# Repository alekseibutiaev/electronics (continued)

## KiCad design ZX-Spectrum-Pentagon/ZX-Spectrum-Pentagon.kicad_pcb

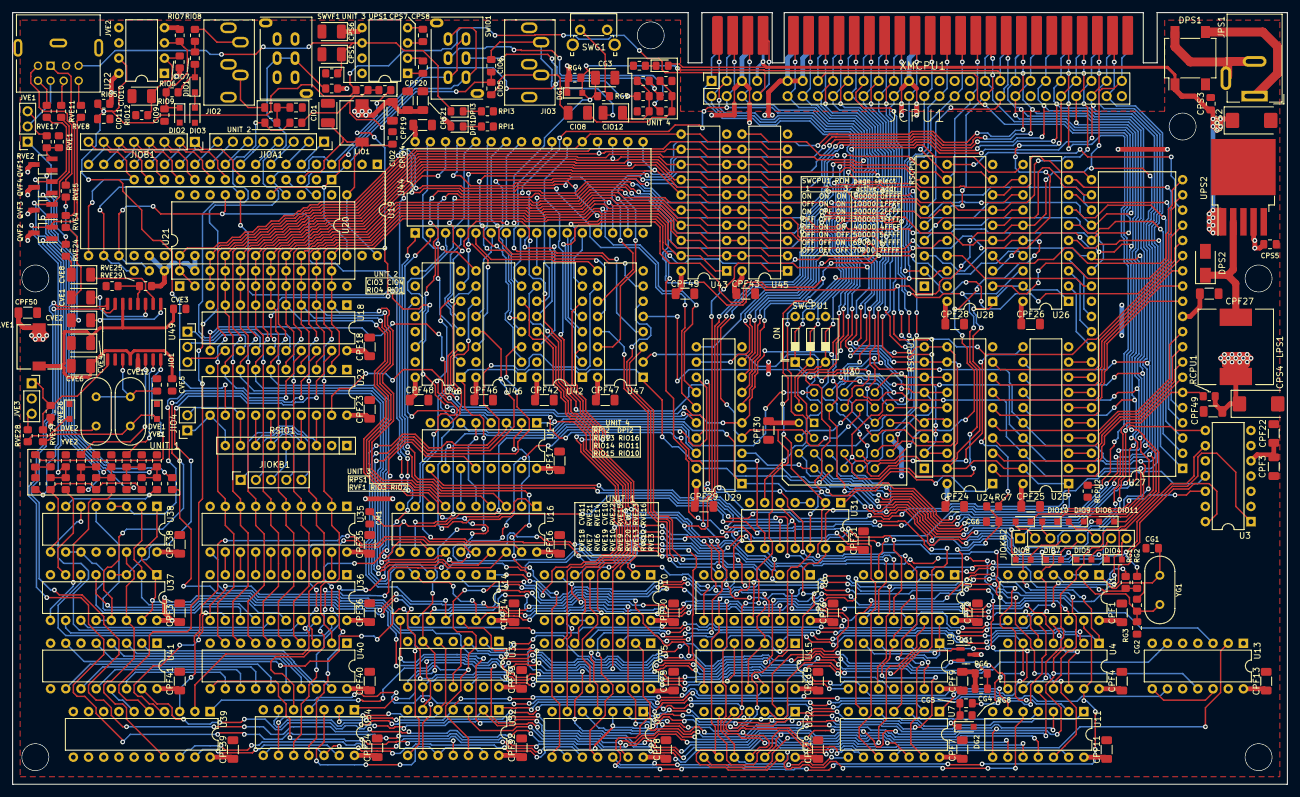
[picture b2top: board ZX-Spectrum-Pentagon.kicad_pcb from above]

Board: 2 copper layers, 213.1 x 129.0 mm, 251 parts (0 on the bottom side), 347 nets.

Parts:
CG1, CG2: 20pF; C_0805_2012Metric_Pad1.18x1.45mm_HandSolder
CG3: 47uF/16V; CP_EIA-3528-21_Kemet-B_Pad1.50x2.35mm_HandSolder
CG4: 1nF; C_0805_2012Metric_Pad1.18x1.45mm_HandSolder
CG5: 22nF; C_0805_2012Metric_Pad1.18x1.45mm_HandSolder
CG6: 510pF; C_0805_2012Metric_Pad1.18x1.45mm_HandSolder
CIO1: 47uF/16V; CP_EIA-3528-21_Kemet-B_Pad1.50x2.35mm_HandSolder
CIO2, CIO11: 100nF; C_0805_2012Metric_Pad1.18x1.45mm_HandSolder
CIO3, CIO5, CIO6, CIO7: 150nF; C_0805_2012Metric_Pad1.18x1.45mm_HandSolder
CIO4: 3.3nF; C_0805_2012Metric_Pad1.18x1.45mm_HandSolder
CIO8, CIO10, CIO12: 10uF/16V; CP_EIA-3528-21_Kemet-B_Pad1.50x2.35mm_HandSolder
CIO9: 1nF; C_0805_2012Metric_Pad1.18x1.45mm_HandSolder
CM1: 1nF; C_0805_2012Metric_Pad1.18x1.45mm_HandSolder
CPF1, CPF2, CPF3, CPF4, CPF5, CPF6, CPF7, CPF8, CPF9, CPF10, CPF11, CPF12, CPF13, CPF14, CPF15, CPF16, CPF17, CPF18, CPF19, CPF20, CPF21, CPF22, CPF23, CPF24, CPF25, CPF26, CPF27, CPF28, CPF29, CPF30, CPF31, CPF32, CPF33, CPF34, CPF35, CPF36, CPF37, CPF38, CPF39, CPF40, CPF41, CPF42, CPF43, CPF44, CPF45, CPF46, CPF47, CPF48, CPF49, CPF50: 100nF; C_1206_3216Metric_Pad1.33x1.80mm_HandSolder
CPS1, CPS6: 4.7uF/16V; CP_EIA-3528-21_Kemet-B_Pad1.50x2.35mm_HandSolder
CPS2, CPS4: 330uF/16V; CP_EIA-7343-31_Kemet-D_Pad2.25x2.55mm_HandSolder
CPS3, CPS5: 100nF; C_0805_2012Metric_Pad1.18x1.45mm_HandSolder
CPS7, CPS8: 1uF; C_0805_2012Metric_Pad1.18x1.45mm_HandSolder
CVE1, CVE2, CVE8: 220uF/6V; CP_EIA-3528-21_Kemet-B_Pad1.50x2.35mm_HandSolder
CVE3, CVE5, CVE7, CVE10, CVE11: 100nF; C_0805_2012Metric_Pad1.18x1.45mm_HandSolder
CVE4, CVE6: 47uF/16V; CP_EIA-3528-21_Kemet-B_Pad1.50x2.35mm_HandSolder
CVE12: 5pF; C_0805_2012Metric_Pad1.18x1.45mm_HandSolder
DG1, DG2: 1N4148; D_SOD-323_HandSoldering
DIO1, DIO3: BZX35450-C3V0X; D_SOD-323_HandSoldering
DIO2, DIO4, DIO5, DIO6, DIO7, DIO8, DIO9, DIO10, DIO11: 1N4148; D_SOD-323_HandSoldering
DPI1: RED; LED_0805_2012Metric_Pad1.15x1.40mm_HandSolder
DPI2: YELLO; LED_0805_2012Metric_Pad1.15x1.40mm_HandSolder
DPI3: GREEN; LED_0805_2012Metric_Pad1.15x1.40mm_HandSolder
DPS1: DF005S; Diode_Bridge_Vishay_DFS
DPS2: SK810; D_SMA
DVE1, DVE2: 1N4148; D_SOD-323_HandSoldering
JCPU1: Conn_02x28; PinSocket_2x28_P2.54mm_Vertical
JIO1: Conn_01x03_Female; PinSocket_1x03_P2.54mm_Vertical
JIO2, JIO3: AudioJack; Jack_3.5mm_CUI_SJ1-3535NG_Vertical
JIO4: Conn_01x02_Female; PinSocket_1x02_P2.54mm_Vertical
JIOA1: Conn_01x08_Female; PinSocket_1x08_P2.54mm_Vertical
JIOB1: Conn_01x08_Female; PinSocket_1x08_P2.54mm_Vertical
JIOKB1: Conn_01x05_Female; PinSocket_1x05_P2.54mm_Vertical
JIOKB2: Conn_01x08_Female; PinSocket_1x08_P2.54mm_Vertical
JPS1: Power_Jack; BarrelJack_Wuerth_6941xx301002
JVE1: SYNC/CVIDEO; PinSocket_1x03_P2.54mm_Vertical
JVE2: SVIDEO; CUI_MD-80SMK
JVE3: PAL/NTSC; PinSocket_1x03_P2.54mm_Vertical
LIO1: 100uH; L_7.3x7.3_H4.5
LPS1: 33uH; L_12x12mm_H6mm
LVE1: 100uH; L_7.3x7.3_H4.5
QG1: BC848; SOT-23
QVF1, QVF2, QVF3, QVF4: BC848; SOT-23_Handsoldering
RCPU1: 330; R_0805_2012Metric_Pad1.20x1.40mm_HandSolder
RCPU2: 10kOm; R_0805_2012Metric_Pad1.20x1.40mm_HandSolder
RG1, RG8: 1kOm; R_0805_2012Metric_Pad1.20x1.40mm_HandSolder
RG2, RG4: 10kOm; R_0805_2012Metric_Pad1.20x1.40mm_HandSolder
RG3: 2MOm; R_0805_2012Metric_Pad1.20x1.40mm_HandSolder
RG5: 330; R_0805_2012Metric_Pad1.20x1.40mm_HandSolder
RG6: 160; R_0805_2012Metric_Pad1.20x1.40mm_HandSolder
RG7: 680; R_0805_2012Metric_Pad1.20x1.40mm_HandSolder
RIO1, RIO3, RIO4: 47kOm; R_0805_2012Metric_Pad1.20x1.40mm_HandSolder
RIO2: 10kOm; R_0805_2012Metric_Pad1.20x1.40mm_HandSolder
RIO5: 2.2kOm; R_0805_2012Metric_Pad1.20x1.40mm_HandSolder
RIO6, RIO11, RIO13: 4.7kOm; R_0805_2012Metric_Pad1.20x1.40mm_HandSolder
RIO7: 100kOm; R_0805_2012Metric_Pad1.20x1.40mm_HandSolder
RIO8: 1kOm; R_0805_2012Metric_Pad1.20x1.40mm_HandSolder
RIO9, RIO15, RIO16: 330; R_0805_2012Metric_Pad1.20x1.40mm_HandSolder
RIO10, RIO14: 3.0kOm; R_0805_2012Metric_Pad1.20x1.40mm_HandSolder
RIO12: 160; R_0805_2012Metric_Pad1.20x1.40mm_HandSolder
RPI1, RPI2, RPI3: 330; R_0805_2012Metric_Pad1.20x1.40mm_HandSolder
RPS1: 4.7kOm; R_0805_2012Metric_Pad1.20x1.40mm_HandSolder
RSCPU1, RSCPU2: 8x10kOm; R_Array_SIP9
RSIO1: 8x10kOm; R_Array_SIP9
RVE1, RVE2: 270; R_0805_2012Metric_Pad1.20x1.40mm_HandSolder
RVE3: 680; R_0805_2012Metric_Pad1.20x1.40mm_HandSolder
RVE4, RVE5, RVE21, RVE22, RVE23, RVE24: 75; R_0805_2012Metric_Pad1.20x1.40mm_HandSolder
RVE6, RVE9, RVE12: 3.9kOm; R_0805_2012Metric_Pad1.20x1.40mm_HandSolder
RVE7, RVE10, RVE13: 18kOm; R_0805_2012Metric_Pad1.20x1.40mm_HandSolder
RVE8, RVE11, RVE17, RVE18, RVE19, RVE20: 68; R_0805_2012Metric_Pad1.20x1.40mm_HandSolder
RVE14, RVE15, RVE16: 2.2kOm; R_0805_2012Metric_Pad1.20x1.40mm_HandSolder
RVE25: 0Om; R_0805_2012Metric_Pad1.20x1.40mm_HandSolder
RVE26, RVE27, RVE28, RVE29: 10kOm; R_0805_2012Metric_Pad1.20x1.40mm_HandSolder
RVF1: 4.7kOm; R_0805_2012Metric_Pad1.20x1.40mm_HandSolder
SWCPU1: ROMSELECT; SW_DIP_SPSTx03_Slide_6.7x9.18mm_W7.62mm_P2.54mm_LowProfile
SWG1: RESET; SW_Tactile_SPST_Angled_PTS645Vx39-2LFS
SWIO1: ABC/ACB; PS-22F03
SWVF1: 128K/512K; PS-22F03
U1, U7: 74HC04; DIP-14_W7.62mm
U2: 74HC14; DIP-14_W7.62mm
U3: 74HC93; DIP-14_W7.62mm
U4: 74HC11; DIP-14_W7.62mm
U5, U10: 74HC193; DIP-16_W7.62mm
U6, U17, U42, U46, U47, U48: 74HC257; DIP-16_W7.62mm
U8, U32: 74HC00; DIP-14_W7.62mm
U9: 74HC86; DIP-14_W7.62mm
U11: 74HC02; DIP-14_W7.62mm
U12, U34: 74HC08; DIP-14_W7.62mm
U13, U15, U33: 74HC74; DIP-14_W7.62mm
U14: 74HC393; DIP-14_W7.62mm
U16: 74HC273; DIP-20_W7.62mm
U18, U35, U36, U40, U45: 74HC574; DIP-20_W7.62mm
U19: AY-3-8910; DIP-40_W15.24mm
U20: AY-3-8912_DUMMY; DIP-28_W15.24mm
U21: AY-3-8913_DUMMY; DIP-24_W15.24mm
U22: LM311; DIP-8_W7.62mm
U23, U24: 74HC245; DIP-20_W7.62mm
U25, U26, U43: 74HC541; DIP-20_W7.62mm
U27: Z80CPU; DIP-40_W15.24mm
U28: 74HC244; DIP-20_W7.62mm
U29, U39: GAL16V8; DIP-20_W7.62mm
U30: 29F040; PLCC-32_THT-Socket
U31: 74HC32; DIP-14_W7.62mm
U37, U38: 74HC153; DIP-16_W7.62mm
U41: 74HC166; DIP-16_W7.62mm
U44: HM628512; DIP-32_W15.24mm
U49: AD724; SOIC-16W_7.5x10.3mm_P1.27mm
UPS1: ST662; DIP-8_W7.62mm
UPS2: LM2596S-5.0V; TO-263-5_TabPin3
XMCPU1: EDGE-28M5; EDGE_28M5-2.54
YG1: 14MHZ; Crystal_HC49-U_Vertical
YVE1: 3.579545MHz OR 14.318180MHz; Crystal_HC49-U_Vertical
YVE2: 4.433619MHz OR 17.734480MHz; Crystal_HC49-U_Vertical

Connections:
+9V: CPS2.1, CPS3.1, DPI2.2 (A), DPS1.1 (+), JCPU1.7, UPS2.1 (VIN), XMCPU1.A4
/+12V: CPS1.1, DPI3.2 (A), JVE2.5, RPS1.1, UPS1.6 (VOut)
/A0: JCPU1.17, U26.16 (B2), U29.8 (I6), U30.12 (A0), U42.5 (A1), XMCPU1.A9
/A1: JCPU1.19, U26.17 (B1), U29.6 (I4), U30.11 (A1), U42.2 (A0), XMCPU1.A10
/A2: JCPU1.21, U26.18 (B0), U30.10 (A2), U42.14 (A3), XMCPU1.A11
/A3: JCPU1.23, U25.11 (B7), U30.9 (A3), U42.11 (A2), XMCPU1.A12
/A4: JCPU1.47, U25.12 (B6), U30.8 (A4), U46.5 (A1), XMCPU1.A24
/A5: JCPU1.45, U25.13 (B5), U29.2 (I0), U30.7 (A5), U46.2 (A0), XMCPU1.A23
/A6: JCPU1.43, U25.14 (B4), U30.6 (A6), U46.14 (A3), XMCPU1.A22
/A7: JCPU1.41, U25.15 (B3), U29.3 (I1), U30.5 (A7), U47.11 (A2), XMCPU1.A21
/A8: DIO6.1 (K), JCPU1.52, U25.16 (B2), U30.27 (A8), U47.14 (A3), XMCPU1.B26
/A9: DIO9.1 (K), JCPU1.53, U25.17 (B1), U30.26 (A9), U47.5 (A1), XMCPU1.A27
/A10: DIO10.1 (K), JCPU1.54, U25.18 (B0), U30.23 (A10), U47.2 (A0), XMCPU1.B27
/A11: DIO11.1 (K), JCPU1.55, U26.15 (B3), U30.25 (A11), U48.5 (A1), XMCPU1.A28
/A12: DIO8.1 (K), JCPU1.3, U26.14 (B4), U30.4 (A12), U48.2 (A0), XMCPU1.A2
/A13: DIO7.1 (K), JCPU1.4, U26.13 (B5), U30.28 (A13), U48.14 (A3), XMCPU1.B2
/A14: DIO5.1 (K), JCPU1.1, U8.5 (B), U17.3 (B0), U17.10 (B2), U26.12 (B6), U29.5 (I3), U31.13 (B), XMCPU1.A1
/A14-ROM: U16.12 (Q4), U30.29 (A14)
/A15: DIO4.1 (K), JCPU1.2, U8.4 (A), U17.6 (B1), U26.11 (B7), U29.1 (CLK), U31.12 (A), XMCPU1.B1
/AYCLK: U3.11 (QB2), U19.22 (CLK), U20.15 (CLK), U21.20 (CLK)
/BC1: U19.29 (BC1), U20.20 (BC1), U21.3 (BC1), U29.15 (IO5)
/BDIR: U19.27 (BDIR), U20.18 (BDIR), U21.2 (BDIR), U29.14 (IO6)
/BL: CG4.1, QG1.2 (E), RG6.2, U37.1 (~G0), U37.15 (~G1), U38.1 (~G0), U38.15 (~G1)
/C3: U1.12 (~Y), U36.11 (C)
/C5: U13.6 (~Q), U37.2 (SE1), U38.2 (SE1)
/C16: U7.10 (~Y), U43.1 (~OE0), U43.19 (~OE1), U44.29 (~WE)
/C17: U32.8 (~Y), U35.11 (C)
/C18: U32.11 (~Y), U40.11 (C)
/C19: U8.11 (~Y), U45.1 (~OE)
/C20: U11.12 (B), U32.6 (~Y), U45.11 (C)
/C25: RCPU1.1, U1.6 (~Y), U4.1 (A), U15.2 (D), U27.6 (~CLK)
/C29: U9.9 (A), U11.6 (B), U32.9 (A), U33.9 (Q)
/C30: U6.1 (~A/B), U32.12 (A), U33.8 (~Q)
/C31: U2.2 (~Y), U2.3 (A), U15.3 (C), U15.11 (C)
/CBRDB: U18.19 (Q0), U37.3 (D03), U37.4 (D02)
/CBRDG: U18.17 (Q2), U38.3 (D03), U38.4 (D02)
/CBRDR: U18.18 (Q1), U37.12 (D12), U37.13 (D13)
/CPU: U32.5 (B), U33.5 (Q), U34.9 (A)
/CPU/BUSACK: U2.6 (~Y), U24.19 (~OE), U25.1 (~OE0), U25.19 (~OE1), U26.1 (~OE0), U26.19 (~OE1), U28.1 (~OE)
/CPU/DIR: U24.1 (A/~B), U29.19 (IO1)
/CPU/RA15: JCPU1.40, RSCPU2.6 (R5), U30.3 (A15), XMCPU1.B20
/CPU/RA16: RSCPU2.7 (R6), SWCPU1.1, U30.2 (A16)
/CPU/RA17: RSCPU2.8 (R7), SWCPU1.2, U30.30 (A17)
/CPU/RA18: RSCPU2.9 (R8), SWCPU1.3, U30.1 (A18)
/CPU/xA0: U26.4 (A2), U27.30 (A0)
/CPU/xA1: U26.3 (A1), U27.31 (A1)
/CPU/xA2: U26.2 (A0), U27.32 (A2)
/CPU/xA3: U25.9 (A7), U27.33 (A3)
/CPU/xA4: U25.8 (A6), U27.34 (A4)
/CPU/xA5: U25.7 (A5), U27.35 (A5)
/CPU/xA6: U25.6 (A4), U27.36 (A6)
/CPU/xA7: U25.5 (A3), U27.37 (A7)
/CPU/xA8: U25.4 (A2), U27.38 (A8)
/CPU/xA9: U25.3 (A1), U27.39 (A9)
/CPU/xA10: U25.2 (A0), U27.40 (A10)
/CPU/xA11: U26.5 (A3), U27.1 (A11)
/CPU/xA12: U26.6 (A4), U27.2 (A12)
/CPU/xA13: U26.7 (A5), U27.3 (A13)
/CPU/xA14: U26.8 (A6), U27.4 (A14)
/CPU/xA15: U26.9 (A7), U27.5 (A15)
/CPU/xD0: U24.8 (A6), U27.14 (D0)
/CPU/xD1: U24.9 (A7), U27.15 (D1)
/CPU/xD2: U24.6 (A4), U27.12 (D2)
/CPU/xD3: U24.3 (A1), U27.8 (D3)
/CPU/xD4: U24.2 (A0), U27.7 (D4)
/CPU/xD5: U24.4 (A2), U27.9 (D5)
/CPU/xD6: U24.5 (A3), U27.10 (D6)
/CPU/xD7: U24.7 (A5), U27.13 (D7)
/CPU/~BUSACK: JCPU1.51, U2.5 (A), U28.7 (B1), XMCPU1.A26
/CPU/~BUSRQ: JCPU1.37, RSCPU2.4 (R3), U27.25 (~BUSRQ), XMCPU1.A19
/CPU/~DI_ULA: JCPU1.25, U29.12 (IO8), XMCPU1.A13
/CPU/~HALT: JCPU1.30, U28.9 (B0), XMCPU1.B15
/CPU/~IORQ: JCPU1.34, U28.16 (B1), U29.7 (I5), XMCPU1.B17
/CPU/~M1: JCPU1.48, U28.5 (B2), U29.9 (I7), XMCPU1.B24
/CPU/~NMI: JCPU1.28, RSCPU2.2 (R1), U27.17 (~NMI), XMCPU1.B14
/CPU/~ROMCE: U30.22 (~CE), U31.6 (Y)
/CPU/~ROMCS: JCPU1.49, RCPU2.1, U31.1 (A), XMCPU1.A25
/CPU/~WAIT: JCPU1.42, RSCPU2.5 (R4), U27.24 (~WAIT), XMCPU1.B21
/CPU/~WR: JCPU1.38, U28.14 (B2), U29.11 (~OE/I8), XMCPU1.B19
/CPU/~xBUSACK: U27.23 (~BUSACK), U28.13 (A1)
/CPU/~xHALT: U27.18 (~HALT), U28.11 (A0)
/CPU/~xIORQ: U27.20 (~IORQ), U28.4 (A1)
/CPU/~xM1: U27.27 (~M1), U28.15 (A2)
/CPU/~xMREQ: U27.19 (~MREQ), U28.2 (A0)
/CPU/~xRD: U27.21 (~RD), U28.8 (A3)
/CPU/~xRFSH: U27.28 (~RFSH), U28.17 (A3)
/CPU/~xWR: U27.22 (~WR), U28.6 (A2)
/CS_32765: CM1.1, U16.11 (WR), U29.18 (IO2)
/D0: JCPU1.12, RSCPU1.8 (R7), U16.3 (D0), U18.2 (D0), U19.37 (D0), U20.28 (D0), U21.11 (D0), U23.2 (A0), U24.12 (B6), U30.13 (D0), U43.2 (A0), U45.19 (Q0), XMCPU1.B6
/D1: JCPU1.14, RSCPU1.9 (R8), U16.4 (D1), U18.3 (D1), U19.36 (D1), U20.27 (D1), U21.10 (D1), U23.3 (A1), U24.11 (B7), U30.14 (D1), U43.3 (A1), U45.18 (Q1), XMCPU1.B7
/D2: JCPU1.16, RSCPU1.6 (R5), U16.7 (D2), U18.4 (D2), U19.35 (D2), U20.26 (D2), U21.9 (D2), U23.4 (A2), U24.14 (B4), U30.15 (D2), U43.4 (A2), U45.17 (Q2), XMCPU1.B8
/D3: JCPU1.22, RSCPU1.3 (R2), U16.8 (D3), U18.5 (D3), U19.34 (D3), U20.25 (D3), U21.8 (D3), U23.5 (A3), U24.17 (B1), U30.17 (D3), U43.5 (A3), U45.16 (Q3), XMCPU1.B11
/D4: JCPU1.24, RSCPU1.2 (R1), U16.13 (D4), U18.6 (D4), U19.33 (D4), U20.24 (D4), U21.7 (D4), U23.6 (A4), U24.18 (B0), U30.18 (D4), U43.6 (A4), U45.15 (Q4), XMCPU1.B12
/D5: JCPU1.20, RSCPU1.4 (R3), U16.14 (D5), U18.7 (D5), U19.32 (D5), U20.23 (D5), U21.6 (D5), U23.7 (A5), U24.16 (B2), U30.19 (D5), U43.7 (A5), U45.14 (Q5), XMCPU1.B10
/D6: JCPU1.18, RSCPU1.5 (R4), U16.17 (D6), U18.8 (D6), U19.31 (D6), U20.22 (D6), U21.5 (D6), U23.8 (A6), U24.15 (B3), U30.20 (D6), U43.8 (A6), U45.13 (Q6), XMCPU1.B9
/D7: JCPU1.6, RSCPU1.7 (R6), U16.18 (D7), U18.9 (D7), U19.30 (D7), U20.21 (D7), U21.4 (D7), U23.9 (A7), U24.13 (B5), U30.21 (D7), U43.9 (A7), U45.12 (Q7), XMCPU1.B3
/DISPLAY: U4.11 (C), U9.10 (B), U31.9 (A), U33.6 (~Q), U34.1 (A), U42.1 (~A/B), U46.1 (~A/B), U47.1 (~A/B), U48.1 (~A/B)
/DI_32765: U16.15 (Q5), U29.13 (IO7)
/F25Hz: U13.9 (Q), U39.1 (CLK)
/FSYNC: U9.6 (Y), U9.13 (B)
/GPA6: U34.13 (B), U39.19 (IO1)
/GPA7: U8.10 (B), U39.18 (IO2)
/Generator/B6: U3.12 (QA0), U6.6 (B1), U14.1 (C)
/Generator/B7: U6.13 (B3), U14.3 (Q0)
/Generator/B8: U6.3 (B0), U14.4 (Q1)
/Generator/B12: U6.5 (A1), U6.10 (B2), U12.9 (A), U12.13 (B), U14.10 (Q1)
/Generator/B13: U6.14 (A3), U11.5 (A), U12.10 (B), U14.9 (Q2)
/Generator/B50: U10.7 (Q3), U11.3 (B), U12.4 (A)
/Generator/B51: U11.9 (B), U12.12 (A), U14.8 (Q3)
/Generator/C6: U11.10 (~Y), U12.5 (B)
/HSYNC: U3.14 (CA), U8.3 (~Y), U9.4 (A), U49.16 (HSYNC)
/InputOutput/CHA: RIO14.1, U19.4 (ACHA), U20.5 (ACHA), U21.17 (ACHA)
/InputOutput/CHB: SWIO1.1 (A), SWIO1.6 (C), U19.3 (ACHB), U20.4 (ACHB), U21.15 (ACHB)
/InputOutput/CHC: SWIO1.3 (C), SWIO1.4 (A), U19.38 (ACHC), U20.1 (ACHC), U21.18 (ACHC)
/InputOutput/IND5: JIO4.2, RSIO1.8 (R7), U23.13 (B5)
/InputOutput/IND7: JIO4.1, RSIO1.9 (R8), U23.11 (B7)
/InputOutput/IOA0: JIOB1.8, U19.21 (IOA0), U20.14 (IOA0)
/InputOutput/IOA1: JIOB1.7, U19.20 (IOA1), U20.13 (IOA1)
/InputOutput/IOA2: JIOB1.6, U19.19 (IOA2), U20.12 (IOA2)
/InputOutput/IOA3: JIOB1.5, U19.18 (IOA3), U20.11 (IOA3)
/InputOutput/IOA4: JIOB1.4, U19.17 (IOA4), U20.10 (IOA4)
/InputOutput/IOA5: JIOB1.3, U19.16 (IOA5), U20.9 (IOA5)
/InputOutput/IOA6: JIOB1.2, U19.15 (IOA6), U20.8 (IOA6)
/InputOutput/IOA7: JIOB1.1, U19.14 (IOA7), U20.7 (IOA7)
/InputOutput/IOB0: JIOA1.8, U19.13 (IOB0)
/InputOutput/IOB1: JIOA1.7, U19.12 (IOB1)
/InputOutput/IOB2: JIOA1.6, U19.11 (IOB2)
/InputOutput/IOB3: JIOA1.5, U19.10 (IOB3)
/InputOutput/IOB4: JIOA1.4, U19.9 (IOB4)
/InputOutput/IOB5: JIOA1.3, U19.8 (IOB5)
/InputOutput/IOB6: JIOA1.2, U19.7 (IOB6)
/InputOutput/IOB7: JIOA1.1, U19.6 (IOB7)
/InputOutput/KBA8: DIO6.2 (A), JIOKB2.6
/InputOutput/KBA9: DIO9.2 (A), JIOKB2.3
/InputOutput/KBA10: DIO10.2 (A), JIOKB2.2
/InputOutput/KBA11: DIO11.2 (A), JIOKB2.1
/InputOutput/KBA12: DIO8.2 (A), JIOKB2.4
/InputOutput/KBA13: DIO7.2 (A), JIOKB2.5
/InputOutput/KBA14: DIO5.2 (A), JIOKB2.7
/InputOutput/KBA15: DIO4.2 (A), JIOKB2.8
/InputOutput/KBD0: JIOKB1.1, RSIO1.3 (R2), U23.18 (B0)
/InputOutput/KBD1: JIOKB1.2, RSIO1.4 (R3), U23.17 (B1)
/InputOutput/KBD2: JIOKB1.3, RSIO1.5 (R4), U23.16 (B2)
/InputOutput/KBD3: JIOKB1.4, RSIO1.6 (R5), U23.15 (B3)
/InputOutput/KBD4: JIOKB1.5, RSIO1.7 (R6), U23.14 (B4)
/InputOutput/OURD5: JIO1.1, U18.14 (Q5)
/InputOutput/OURD6: JIO1.2, U18.13 (Q6)
/InputOutput/OURD7: JIO1.3, U18.12 (Q7)
/InputOutput/TYPEOUTTTL: RIO1.1, RIO4.1, U18.16 (Q3)
/InputOutput/TapeIn: JIO2.T, RIO8.1
/InputOutput/TapeOut: CIO3.2, JIO2.R
/MD0: U35.2 (D0), U40.2 (D0), U43.18 (B0), U44.13 (D0), U45.2 (D0)
/MD1: U35.3 (D1), U40.3 (D1), U43.17 (B1), U44.14 (D1), U45.3 (D1)
/MD2: U35.4 (D2), U40.4 (D2), U43.16 (B2), U44.15 (D2), U45.4 (D2)
/MD3: U35.5 (D3), U40.5 (D3), U43.15 (B3), U44.17 (D3), U45.5 (D3)
/MD4: U35.6 (D4), U40.6 (D4), U43.14 (B4), U44.18 (D4), U45.6 (D4)
/MD5: U35.7 (D5), U40.7 (D5), U43.13 (B5), U44.19 (D5), U45.7 (D5)
/MD6: U35.8 (D6), U40.8 (D6), U43.12 (B6), U44.20 (D6), U45.8 (D6)
/MD7: U35.9 (D7), U40.9 (D7), U43.11 (B7), U44.21 (D7), U45.9 (D7)
/MX0: U17.4 (Y0), U48.11 (A2)
/MX1: U17.7 (Y1), U46.11 (A2)
/MX2: U17.9 (Y2), U31.10 (B)
/MX3: U17.12 (Y3), U34.10 (B)
/Memory/MA0: U42.7 (Y1), U44.12 (A0)
/Memory/MA1: U42.4 (Y0), U44.11 (A1)
/Memory/MA2: U42.12 (Y3), U44.10 (A2)
/Memory/MA3: U42.9 (Y2), U44.9 (A3)
/Memory/MA4: U44.8 (A4), U46.7 (Y1)
/Memory/MA5: U44.7 (A5), U46.4 (Y0)
/Memory/MA6: U44.6 (A6), U46.12 (Y3)
/Memory/MA7: U44.5 (A7), U47.9 (Y2)
/Memory/MA8: U44.27 (A8), U47.12 (Y3)
/Memory/MA9: U44.26 (A9), U47.7 (Y1)
/Memory/MA10: U44.23 (A10), U47.4 (Y0)
/Memory/MA11: U44.25 (A11), U48.7 (Y1)
/Memory/MA12: U44.4 (A12), U48.4 (Y0)
/Memory/MA13: U44.28 (A13), U48.12 (Y3)
/Memory/MA14: U44.3 (A14), U48.9 (Y2)
/Memory/MA15: U44.31 (A15), U46.9 (Y2)
/Memory/MA16: U31.8 (Y), U44.2 (A16)
/Memory/MA17: U34.11 (~Y), U44.30 (A17)
/Memory/MA18: U8.8 (~Y), U44.1 (A18)
/PA6: U16.16 (Q6), U39.2 (I0)
/PA7: U16.19 (Q7), U39.3 (I1)
/PowerSources/PowA: DPS1.3, JPS1.1
/PowerSources/PowB: DPS1.4, JPS1.2, JPS1.3
/RAS: U15.5 (Q), U15.12 (D), U32.4 (A), U34.2 (B)
/SA0: U5.6 (Q2), U13.3 (C), U42.6 (B1)
/SA1: U5.7 (Q3), U42.3 (B0)
/SA2: U7.1 (A), U10.3 (Q0), U42.13 (B3)
/SA3: U10.2 (Q1), U11.2 (A), U42.10 (B2)
/SA4: U10.6 (Q2), U12.2 (B), U46.6 (B1)
/SA5: U14.5 (Q2), U46.3 (B0)
/SA6: U4.4 (B), U14.6 (Q3), U14.13 (C), U46.13 (B3)
/SA7: U4.5 (C), U14.11 (Q0), U47.10 (B2)
/SA8: U6.7 (Y1), U47.13 (B3)
/SA9: U6.12 (Y3), U47.6 (B1)
/SA10: U6.4 (Y0), U47.3 (B0)
/SA11: U6.9 (Y2), U48.6 (B1)
/SA12: U7.4 (~Y), U48.3 (B0)
/SCRSEL: U16.9 (Q3), U46.10 (B2)
/TAPEINTTL: CIO11.2, JCPU1.8, RIO3.2, RIO5.1, U22.7, U23.12 (B6), XMCPU1.B4
/TTLB: RVE6.2, U37.7 (Y0)
/TTLG: RVE12.2, U38.7 (Y0)
/TTLR: RVE9.2, U37.9 (Y1)
/TTLSYNC: RVE3.2, U9.11 (Y)
/TTLY: RVE7.2, RVE10.2, RVE13.2, U38.9 (Y1)
/VSYNC: U2.12 (~Y), U49.15 (VSYNC)
/VideoEncoder/BLUE: JVE2.8, RVE8.2
/VideoEncoder/CRMA: JVE2.3, RVE5.1
/VideoEncoder/CVIDEO: JVE1.1, RVE24.1
/VideoEncoder/GREEN: JVE2.6, RVE17.2
/VideoEncoder/LUMA: JVE2.1, RVE4.1
/VideoEncoder/RED: JVE2.7, RVE11.2
/VideoEncoder/SYNC: JVE1.3, RVE2.1
/VideoEncoder/VIDEO: JVE1.2, JVE2.4
/VideoFormating/512KMOD: RVF1.2, SWVF1.2 (B), SWVF1.5 (B), U39.5 (I3)
/VideoFormating/BLUE_B: U36.16 (Q3), U37.5 (D01)
/VideoFormating/BLUE_F: U36.19 (Q0), U37.6 (D00)
/VideoFormating/BRIGHT: U36.13 (Q6), U38.10 (D10), U38.11 (D11)
/VideoFormating/FLASL_BIT: U36.12 (Q7), U39.4 (I2)
/VideoFormating/GREEN_B: U36.14 (Q5), U38.5 (D01)
/VideoFormating/GREEN_F: U36.17 (Q2), U38.6 (D00)
/VideoFormating/RED_B: U36.15 (Q4), U37.11 (D11)
/VideoFormating/RED_F: U36.18 (Q1), U37.10 (D10)
/VideoFormating/SERDATA: U39.6 (I4), U41.13 (Q)
/~C1: U1.8 (~Y), U41.7 (CLK)
/~C2: U1.10 (~Y), U41.15 (SH/~LD)
/~C25: JCPU1.15, U1.5 (A), U3.8 (QB1), U5.5 (UP), XMCPU1.A8
/~CAS: U15.8 (~Q), U33.3 (C), U33.11 (C), U44.22 (~CE)
/~FQUATER: U31.5 (B), U31.11 (Y), U34.5 (B)
/~IN254: U23.19 (~OE), U29.16 (IO4)
/~INT: JCPU1.26, RG7.1, U27.16 (~INT), XMCPU1.B13
/~MREQ: JCPU1.32, U7.13 (A), U28.18 (B0), U31.2 (B), XMCPU1.B16
/~OUT254: U18.11 (C), U29.17 (I03)
/~RD: JCPU1.36, U7.9 (A), U28.12 (B3), U29.4 (I2), U30.24 (~OE), U32.1 (A), XMCPU1.B18
/~RESET: CG3.1, DG1.2 (A), JCPU1.39, RG4.2, RG5.1, U2.9 (A), XMCPU1.A20
/~RFSH: JCPU1.50, U4.9 (A), U28.3 (B3), XMCPU1.B25
/~RST: RSCPU2.3 (R2), U2.10 (~Y), U16.1 (R), U19.23 (~RESET), U20.16 (~RESET), U21.21 (~RESET), U27.26 (~RESET)
AYVCC: CIO1.1, CIO2.1, LIO1.2, U19.40 (AYVCC), U20.3 (AYVCC), U21.13 (AYVCC)
GND: CG1.2, CG2.1, CG3.2, CG4.2, CG6.1, CIO1.2, CIO2.2, CIO4.2, CIO9.2, CIO10.2, CIO11.1, CM1.2, CPF1.2, CPF2.2, CPF3.2, CPF4.2, CPF5.2, CPF6.2, CPF7.2, CPF8.2, CPF9.2, CPF10.2, CPF11.2, CPF12.2, CPF13.2, CPF14.2, CPF15.2, CPF16.2, CPF17.2, CPF18.2, CPF19.2, CPF20.2, CPF21.2, CPF22.2, CPF23.2, CPF24.2, CPF25.2, CPF26.2, CPF27.2, CPF28.2, CPF29.2, CPF30.2, CPF31.2, CPF32.2, CPF33.2, CPF34.2, CPF35.2, CPF36.2, CPF37.2, CPF38.2, CPF39.2, CPF40.2, CPF41.2, CPF42.2, CPF43.2, CPF44.2, CPF45.2, CPF46.2, CPF47.2, CPF48.2, CPF49.2, CPF50.2, CPS1.2, CPS2.2, CPS3.2, CPS4.2, CPS5.2, CPS6.2, CVE3.2, CVE4.2, CVE5.2, CVE6.2, CVE12.2, DG2.2 (A), DIO2.2 (A), DIO3.2 (A), DPS1.2 (-), DPS2.2 (A), DVE1.1 (K), DVE2.1 (K), JCPU1.11, JCPU1.13, JCPU1.27, JIO2.S, JIO3.S, JVE2.2, JVE2.S1, JVE2.S2, JVE2.S3, JVE3.2, RCPU2.2, RG6.1, RG8.1, RIO7.1, RIO12.2, RIO15.2, RIO16.2, RPI1.2, RPI2.2, RPI3.2, RPS1.2, RVE1.1, RVE14.2, RVE15.2, RVE16.2, RVE21.2, RVE22.2, RVE23.2, RVE29.2, SWCPU1.4, SWCPU1.5, SWCPU1.6, SWG1.2, SWIO1.7, SWIO1.8, SWVF1.1 (A), SWVF1.4 (A), SWVF1.7, SWVF1.8, U1.7 (GND), U2.7 (GND), U3.2 (R0), U3.3 (R1), U3.10 (GND), U4.7 (GND), U5.8 (GND), U5.14 (R), U6.2 (A0), U6.8 (GND), U6.15 (~EZ), U7.7 (GND), U8.7 (GND), U9.7 (GND), U9.12 (A), U10.1 (D1), U10.8 (GND), U10.9 (D3), U10.10 (D2), U10.14 (R), U11.7 (GND), U12.7 (GND), U13.7 (GND), U14.2 (R), U14.7 (GND), U15.7 (GND), U16.10 (GND), U17.8 (GND), U17.13 (B3), U17.15 (~OE), U18.1 (~OE), U18.10 (GND), U19.1 (GND), U19.24 (~A9), U20.6 (GND), U21.1 (GND), U21.19 (GND), U21.22 (~A9), U21.24 (~CS), U22.1 (GND), U22.4 (V-), U23.1 (A/~B), U23.10 (GND), U24.10 (GND), U25.10 (GND), U26.10 (GND), U27.29 (GND), U28.10 (GND), U28.19 (~OE), U29.10 (GND), U30.16 (GND), U31.7 (GND), U32.7 (GND), U33.7 (GND), U34.7 (GND), U35.1 (~OE), U35.10 (GND), U36.1 (~OE), U36.10 (GND), U37.8 (GND), U38.8 (GND), U38.12 (D12), U38.13 (D13), U39.10 (GND), U40.1 (~OE), U40.10 (GND), U41.1 (SER), U41.6 (LCK), U41.8 (GND), U42.8 (GND), U42.15 (~OE), U43.10 (GND), U44.16 (GND), U44.24 (~OE), U45.10 (GND), U46.8 (GND), U46.15 (~OE), U47.8 (GND), U47.15 (~OE), U48.8 (GND), U48.13 (B3), U48.15 (~OE), U49.2 (AGND), U49.13 (DGND), UPS1.7 (GND), UPS1.8 (SHLD), UPS2.3 (GND), UPS2.5 (~ON/OFF), XMCPU1.A6, XMCPU1.A7, XMCPU1.A14
unnamed: CG1.1, RG3.1, U1.1 (A), YG1.1
unnamed: CG2.2, RG3.2, U1.2 (~Y), U1.3 (A), YG1.2
unnamed: CG5.1, DG2.1 (K), RG8.2, U7.5 (A)
unnamed: CG5.2, U2.13 (A), U4.6 (Y), U9.1 (A), U9.5 (B)
unnamed: CG6.2, RG7.2, U7.6 (~Y)
unnamed: CIO3.1, CIO4.1, RIO4.2
unnamed: CIO5.1, CIO6.1, RIO1.2, RIO2.2, RIO3.1
unnamed: CIO5.2, CIO8.2, JIO3.R
unnamed: CIO7.1, RIO8.2
unnamed: CIO7.2, DIO1.2 (A), RIO9.1
unnamed: CIO8.1, RIO10.2, RIO11.2, RIO16.1
unnamed: CIO9.1, DIO2.1 (K), RIO7.2, RIO9.2, U22.3 (-)
unnamed: CIO10.1, RIO6.2, RIO12.1, U22.2 (+)
unnamed: CIO12.1, RIO13.2, RIO14.2, RIO15.1
unnamed: CIO6.2, CIO12.2, JIO3.T
unnamed: CPS7.1, UPS1.1 (C1-)
unnamed: CPS7.2, UPS1.2 (C1+)
unnamed: CPS8.1, UPS1.3 (C2-)
unnamed: CPS8.2, UPS1.4 (C2+)
unnamed: CVE1.1, U49.11 (LUMA)
unnamed: CVE1.2, RVE4.2
unnamed: CVE2.1, U49.9 (CRMA)
unnamed: CVE2.2, RVE5.2
unnamed: CVE3.1, CVE4.1, CVE5.1, CVE6.1, LVE1.2, U49.4 (APOS), U49.14 (DPOS)
unnamed: CVE7.1, RVE20.2, RVE23.1
unnamed: CVE7.2, U49.7 (GIN)
unnamed: CVE8.1, U49.10 (COMP)
unnamed: CVE8.2, RVE24.2
unnamed: CVE10.1, RVE19.2, RVE22.1
unnamed: CVE10.2, U49.6 (RIN)
unnamed: CVE11.1, RVE18.2, RVE21.1
unnamed: CVE11.2, U49.8 (BIN)
unnamed: CVE12.1, U49.3 (FIN), YVE1.1, YVE2.1
unnamed: DIO1.1 (K), DIO3.1 (K)
unnamed: DPI1.1 (K), RPI1.1
unnamed: DPI2.1 (K), RPI2.1
unnamed: DPI3.1 (K), RPI3.1
unnamed: DPS2.1 (K), LPS1.1, UPS2.2 (OUT)
unnamed: DVE1.2 (A), RVE27.1, YVE1.2
unnamed: DVE2.2 (A), RVE28.1, YVE2.2
unnamed: JVE3.1, RVE26.2, RVE27.2, U49.1 (NTSC/~PAL)
unnamed: JVE3.3, RVE28.2
unnamed: QG1.1 (B), U9.3 (Y)
unnamed: QVF1.1 (B), RVE3.1
unnamed: QVF1.2 (E), RVE1.2, RVE2.2
unnamed: QVF2.1 (B), RVE6.1, RVE7.1, RVE14.1
unnamed: QVF2.2 (E), RVE8.1, RVE18.1
unnamed: QVF3.1 (B), RVE9.1, RVE10.1, RVE15.1
unnamed: QVF3.2 (E), RVE11.1, RVE19.1
unnamed: QVF4.1 (B), RVE12.1, RVE13.1, RVE16.1
unnamed: QVF4.2 (E), RVE17.1, RVE20.1
unnamed: RG1.1, U1.4 (~Y)
unnamed: RG1.2, RG2.1, U2.1 (A)
unnamed: RG2.2, U2.4 (~Y), U3.1 (CB)
unnamed: RG5.2, SWG1.1
unnamed: RIO2.1, U18.15 (Q4)
unnamed: RIO10.1, SWIO1.2 (B)
unnamed: RIO11.1, RIO13.1, SWIO1.5 (B)
unnamed: RVE25.2, RVE29.1, U49.12 (4FSC/~FSC)
unnamed: U1.9 (A), U3.9 (QB0)
unnamed: U1.11 (A), U4.12 (Y)
unnamed: U1.13 (A), U4.13 (C), U5.2 (Q1)
unnamed: U2.8 (~Y), U2.11 (A)
unnamed: U4.2 (B), U5.3 (Q0)
unnamed: U7.2 (~Y), U8.1 (A)
unnamed: U7.8 (~Y), U8.12 (A)
unnamed: U5.12 (~CR), U10.5 (UP)
unnamed: U10.11 (~LD), U10.12 (~CR)
unnamed: U8.2 (B), U11.1 (~Y), U12.1 (A)
unnamed: U7.3 (A), U11.4 (~Y)
unnamed: U4.3 (A), U11.8 (A), U12.8 (~Y), U13.11 (C)
unnamed: U11.11 (A), U32.3 (~Y)
unnamed: U7.11 (A), U11.13 (~Y)
unnamed: U9.2 (B), U12.3 (~Y)
unnamed: U12.6 (~Y), U13.2 (D)
unnamed: U12.11 (~Y), U14.12 (R)
unnamed: U13.8 (~Q), U13.12 (D)
unnamed: U16.2 (Q0), U17.2 (A0)
unnamed: U16.5 (Q1), U17.5 (A1)
unnamed: U16.6 (Q2), U17.11 (A2)
unnamed: U8.6 (~Y), U17.1 (~A/B)
unnamed: U31.3 (Y), U31.4 (A)
unnamed: U4.10 (B), U8.13 (B), U32.2 (B), U34.6 (~Y)
unnamed: U32.10 (B), U32.13 (B), U34.3 (~Y)
unnamed: U4.8 (Y), U33.2 (D)
unnamed: U9.8 (Y), U33.12 (D)
unnamed: U7.12 (~Y), U34.4 (A)
unnamed: U8.9 (A), U34.8 (~Y), U34.12 (A)
unnamed: U35.12 (Q7), U36.9 (D7)
unnamed: U35.13 (Q6), U36.8 (D6)
unnamed: U35.14 (Q5), U36.7 (D5)
unnamed: U35.15 (Q4), U36.6 (D4)
unnamed: U35.16 (Q3), U36.5 (D3)
unnamed: U35.17 (Q2), U36.4 (D2)
unnamed: U35.18 (Q1), U36.3 (D1)
unnamed: U35.19 (Q0), U36.2 (D0)
unnamed: U37.14 (SE0), U38.14 (SE0), U39.17 (I03)
unnamed: U40.12 (Q7), U41.14 (D7)
unnamed: U40.13 (Q6), U41.12 (D6)
unnamed: U40.14 (Q5), U41.11 (D5)
unnamed: U40.15 (Q4), U41.10 (D4)
unnamed: U40.16 (Q3), U41.5 (D3)
unnamed: U40.17 (Q2), U41.4 (D2)
unnamed: U40.18 (Q1), U41.3 (D1)
unnamed: U40.19 (Q0), U41.2 (D0)
VCC: CPF1.1, CPF2.1, CPF3.1, CPF4.1, CPF5.1, CPF6.1, CPF7.1, CPF8.1, CPF9.1, CPF10.1, CPF11.1, CPF12.1, CPF13.1, CPF14.1, CPF15.1, CPF16.1, CPF17.1, CPF18.1, CPF19.1, CPF20.1, CPF21.1, CPF22.1, CPF23.1, CPF24.1, CPF25.1, CPF26.1, CPF27.1, CPF28.1, CPF29.1, CPF30.1, CPF31.1, CPF32.1, CPF33.1, CPF34.1, CPF35.1, CPF36.1, CPF37.1, CPF38.1, CPF39.1, CPF40.1, CPF41.1, CPF42.1, CPF43.1, CPF44.1, CPF45.1, CPF46.1, CPF47.1, CPF48.1, CPF49.1, CPF50.1, CPS4.1, CPS5.1, CPS6.1, DG1.1 (K), DPI1.2 (A), JCPU1.5, LIO1.1, LPS1.2, LVE1.1, QG1.3 (C), QVF1.3 (C), QVF2.3 (C), QVF3.3 (C), QVF4.3 (C), RCPU1.2, RG4.1, RIO5.2, RIO6.1, RSCPU1.1 (COM), RSCPU2.1 (COM), RSIO1.1 (COM), RVE25.1, RVE26.1, RVF1.1, U1.14 (VCC), U2.14 (VCC), U3.5 (VCC), U4.14 (VCC), U5.1 (D1), U5.4 (DW), U5.9 (D3), U5.10 (D2), U5.11 (~LD), U5.15 (D0), U5.16 (VCC), U6.11 (A2), U6.16 (VCC), U7.14 (VCC), U8.14 (VCC), U9.14 (VCC), U10.4 (DW), U10.15 (D0), U10.16 (VCC), U11.14 (VCC), U12.14 (VCC), U13.1 (~R), U13.4 (~S), U13.10 (~S), U13.13 (~R), U13.14 (VCC), U14.14 (VCC), U15.1 (~R), U15.4 (~S), U15.10 (~S), U15.13 (~R), U15.14 (VCC), U16.20 (VCC), U17.14 (A3), U17.16 (VCC), U18.20 (VCC), U19.25 (A8), U19.28 (BC2), U20.17 (A8), U20.19 (BC2), U21.23 (A8), U22.8 (V+), U23.20 (VCC), U24.20 (VCC), U25.20 (VCC), U26.20 (VCC), U27.11 (VCC), U28.20 (VCC), U29.20 (VCC), U30.31 (~WE), U30.32 (VCC), U31.14 (VCC), U32.14 (VCC), U33.1 (~R), U33.4 (~S), U33.10 (~S), U33.13 (~R), U33.14 (VCC), U34.14 (VCC), U35.20 (VCC), U36.20 (VCC), U37.16 (VCC), U38.16 (VCC), U39.7 (I5), U39.8 (I6), U39.9 (I7), U39.11 (~OE/I8), U39.20 (VCC), U40.20 (VCC), U41.9 (~R), U41.16 (VCC), U42.16 (VCC), U43.20 (VCC), U44.32 (VCC), U45.20 (VCC), U46.16 (VCC), U47.16 (VCC), U48.10 (B2), U48.16 (VCC), U49.5 (ENCD), UPS1.5 (VCC), UPS2.4 (FB), XMCPU1.A3
